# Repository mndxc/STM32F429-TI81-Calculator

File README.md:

# Neo-81: bringing new life to the classic.

## Why

The TI-81 was the first graphing calculator that was genuinely accessible for learning — affordable, approachable, and in the hands of a generation of students. It also has a look that hasn't aged: boxy, purposeful, built to last.

The problem is that the originals are now 30+ years old and the displays are failing. Rather than let them become landfill, this project replaces the internals while keeping everything that made the hardware iconic. A fresh screen, a modern MCU, and the same keypad you already know.

The end goal is a calculator you can actually use — not a shelf piece. That means completing the feature set, finishing the custom PCB, and ending up with something better than the original: same form factor, same feel, working display, and no artificial limits on what it can do.

---

## Hardware

STM32F429I-DISC1 (Cortex-M4, 180 MHz, 2.4" ILI9341 display, 8 MB SDRAM) with a salvaged TI-81 key matrix wired to the GPIO header.

**Software:** LVGL v9 · FreeRTOS · GCC ARM · CMake

---

## Status

~95% of the original TI-81 guidebook is implemented and daily-usable on the STM32F429I-DISC1 development board. Hardware validation is ongoing — see [docs/hardware_checklist.md](docs/hardware_checklist.md). A custom PCB to replace the original TI-81 internals while keeping the original shell is in design: an STM32H743 main board carrying its own 50-key keypad, plus a small display carrier board that mounts the new 2.8" panel on the original screw posts. See [hardware/](hardware/README.md).

---

## No hardware? No problem.

You can build and run the full test suite on any machine — no STM32 board required.

```bash
git clone https://github.com/mndxc/STM32F429-TI81-Calculator.git
cd STM32F429-TI81-Calculator
cmake -S App/Tests -B build-tests && cmake --build build-tests
ctest --test-dir build-tests
```

All host tests pass on plain x86/ARM Linux and macOS with any standard C compiler — see [docs/TESTING.md](docs/TESTING.md) for the current suite breakdown (16 suites, 1112 assertions). No toolchain, no board, no USB cable needed.

---

## Documentation

| I want to… | Go here |
|---|---|
| Build and flash the firmware | [docs/GETTING_STARTED.md](docs/GETTING_STARTED.md) |
| Understand the architecture | [docs/ARCHITECTURE.md](docs/ARCHITECTURE.md) |
| Read the full technical reference | [docs/TECHNICAL.md](docs/TECHNICAL.md) |
| Run the host tests | [docs/TESTING.md](docs/TESTING.md) |
| Troubleshoot common issues | [docs/TROUBLESHOOTING.md](docs/TROUBLESHOOTING.md) |
| See development process standards | [docs/MAINTENANCE_STANDARDS.md](docs/MAINTENANCE_STANDARDS.md) |
| Understand display stability and power-off behaviour | [docs/DISPLAY_STABILITY.md](docs/DISPLAY_STABILITY.md) |
| Understand power management and Stop mode | [docs/POWER_MANAGEMENT.md](docs/POWER_MANAGEMENT.md) |
| Contribute | [CONTRIBUTING.md](CONTRIBUTING.md) |
| Design the hardware (boards, enclosure) | [hardware/README.md](hardware/README.md) |

---

## What's not in this repo

Some reference material can't be published (it's copyrighted by TI or by part vendors) or is too large to be useful in git. It all lives in **one** local folder, `_reference/`, which `.gitignore` excludes as a whole. Nothing else in the tree is hand-placed and ignored; the other `.gitignore` entries are tool output (builds, caches, backups).

| `_reference/…` | What it holds | Where to get it |
|---|---|---|
| `guidebook/` | The TI-81 Guidebook (PDF and a Markdown transcription). It is the behavioural spec for every calculator feature | TI's original manual: any TI-81 guidebook scan or the printed booklet |
| `datasheets/` | Vendor datasheets for the parts in [docs/PCB_DESIGN.md](docs/PCB_DESIGN.md) and `hardware/` | Each manufacturer's product page (part numbers are in the docs) |
| `kicad-libs/` | Downloaded KiCad libraries, e.g. the CDFER JLCPCB library | KiCad's Plugin and Content Manager |
| `TI-81 Stuff/` | Teardown photos and measurements of original TI-81s | Your own calculator |

You don't need any of it to build the firmware or run the tests.

---

## Contributing

Contributions are welcome — bug fixes, feature work, or documentation improvements. See [CONTRIBUTING.md](CONTRIBUTING.md) for guidelines. All contributors are expected to follow the [Code of Conduct](CODE_OF_CONDUCT.md).

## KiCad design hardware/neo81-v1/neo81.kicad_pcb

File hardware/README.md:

# Neo-81 hardware

Everything for the physical calculator: boards, libraries and enclosure. The firmware is at the repo root, and the board design notes are in [`docs/PCB_DESIGN.md`](../docs/PCB_DESIGN.md).

| Folder | What it is | Status |
|---|---|---|
| [`h7b0-board/`](h7b0-board/) | **Next board**: STM32H743V (was H7B0), RT9471 charger, RT8059 buck, W25Q128 flash, own 50-key keypad; plus a display carrier board | Pin plan and parts list; no KiCad project yet |
| [`neo81-v1/`](neo81-v1/) | First board: keypad + power (IP5310 power bank SoC, 50 touch keys), 6-layer; connects to the STM32F429 Discovery via the J4 header. Its schematic also held an MCU draft, now in `unused-sheets/` | KiCad project plus prepared gerber/BOM/CPL exports; **never ordered** |
| [`libs/`](libs/) | Project KiCad libraries: EasyEDA/LCSC parts, IP5310, JP-USB-C, softKey key footprints | Both boards use them through `${KIPRJMOD}/../libs` |
| [`enclosure/`](enclosure/) | FreeCAD: front shell, keypad PCB outline, key footprint model; `PCBPlan.pages` | Early (Oct–Nov 2025) |
| [`KICAD_CONVENTIONS.md`](KICAD_CONVENTIONS.md) | How symbols, fields, BOM flags, rules and libraries are set up, and the pre-order checklist | Read before any KiCad work |

Datasheets, the TI-81 guidebook, teardown photos and downloaded KiCad libraries are local only, in `../_reference/` (see [What's not in this repo](../README.md#whats-not-in-this-repo)).

## Opening a board in KiCad (10.x)

1. Open `neo81-v1/neo81.kicad_pro`. Its `sym-lib-table` and `fp-lib-table` load `libs/`, so the project works from any path or clone without global library setup.
2. **The JLCPCB library is not in the repo.** Four parts (`PCM_JLCPCB-*`) come from the CDFER JLCPCB library. Install it once with *Plugin and Content Manager → Install from File…* and pick the downloaded zip (kept locally at `_reference/kicad-libs/third-party/com.github.CDFER.JLCPCB-Kicad-Library_v2025.07.18.zip`). You can also install it straight from the PCM catalogue.
3. Checks after the 2026-11-27 cleanup (`kicad-cli` 10.0.0): ERC has **1 error**: IP5310 pin 31 (LIGHT, an output) is tied to GND. Check that against the IP5310 datasheet. DRC with parity: 0 parity issues and 0 unconnected pads. The 7 starved-thermal and 6 USB-C edge-clearance findings are real copper items for the next spin. `unused-sheets/` holds the draft MCU sheet and two orphan sheets that aren't part of this board. Library messages:
   - `PCM_JLCPCB` / `PCM_JLCPCB-Diodes` not configured. Step 2 fixes this.
   - `STM32F429IITx_multi` isn't in KiCad 10's `MCU_ST_STM32F4`. The schematic uses its own stored copy.
   - Several "doesn't match copy in library" warnings. The board and schematic keep their own copies of each part; **don't run "Update from Library" in bulk** without reviewing the changes.
   - The softKey footprints refer to 3D models (`footprintv1.wrl`, `Unnamed.wrl`) that were never exported. Only the 3D view is affected. The source is `enclosure/footprintv1.FCStd`.

## Ordering and assembly

- `neo81-v1/fab-outputs/`: `jlcpcb/production_files/` holds the JLCPCB plugin export (gerbers, `BOM-neo81.csv`, `CPL-neo81.csv`). `manual-gerbers/` is a hand export, and `bom-cpl/` holds its position files. Three zipped gerber sets are export variants that were prepared but never ordered: `neo81v01.zip` (2025-11-19), `neo81MarkH.zip` (2025-11-13), and `neo81TwoBoard.zip` (2026-02-04).
- Before ordering a new board, check the parts in [`h7b0-board/PARTS_VERIFICATION.md`](h7b0-board/PARTS_VERIFICATION.md). Some library footprints must be swapped, and there are open design items.

## What git tracks

The design files are committed: `.kicad_pro`, `.kicad_sch`, `.kicad_pcb`, lib tables, project libraries, FreeCAD and fab outputs. Tool output is ignored by pattern: KiCad backups (`*-backups/`, `*-bkp-*`), caches (`*.kicad_prl`, `fp-info-cache`) and FreeCAD backups (`*.FCBak`). Datasheets and downloaded libraries are local only, under `_reference/`; see the root `.gitignore`.

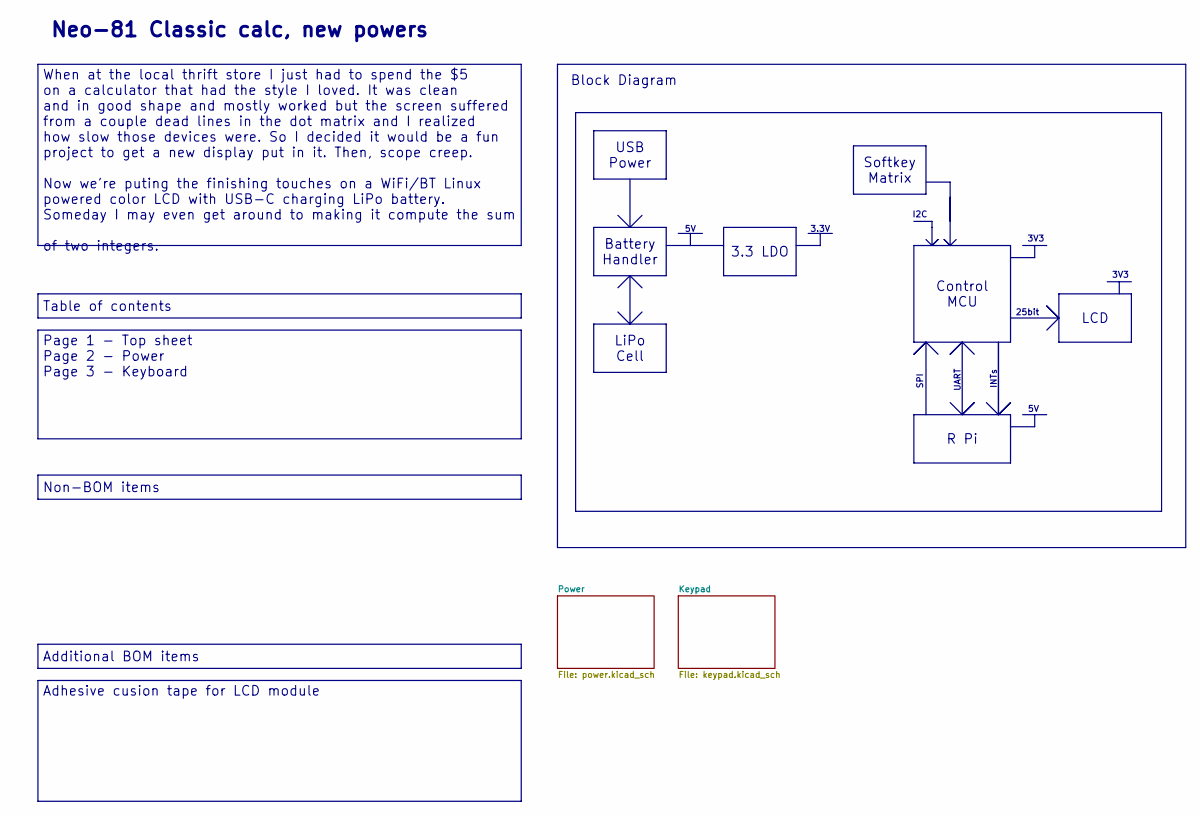
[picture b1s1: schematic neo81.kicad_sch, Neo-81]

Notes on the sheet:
INTs
Neo-81 Classic calc, new powers
Block Diagram
SPI
3V3
I2C
UART
3.3V
25bit
Control MCU
Table of contents
LCD
Non-BOM items
R Pi
Additional BOM items
When at the local thrift store I just had to spend the $5 on a calculator that had the style I loved. It was clean and in good shape and mostly worked but the screen suffered from a couple dead lines in the dot matrix and I realized how slow those devices were. So I decided it would be a fun projec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
Page 1 - Top sheet Page 2 - Power Page 3 - Keyboard
Adhesive cusion tape for LCD module
3.3 LDO
USB Power
Softkey Matrix
Battery Handler
LiPo Cell

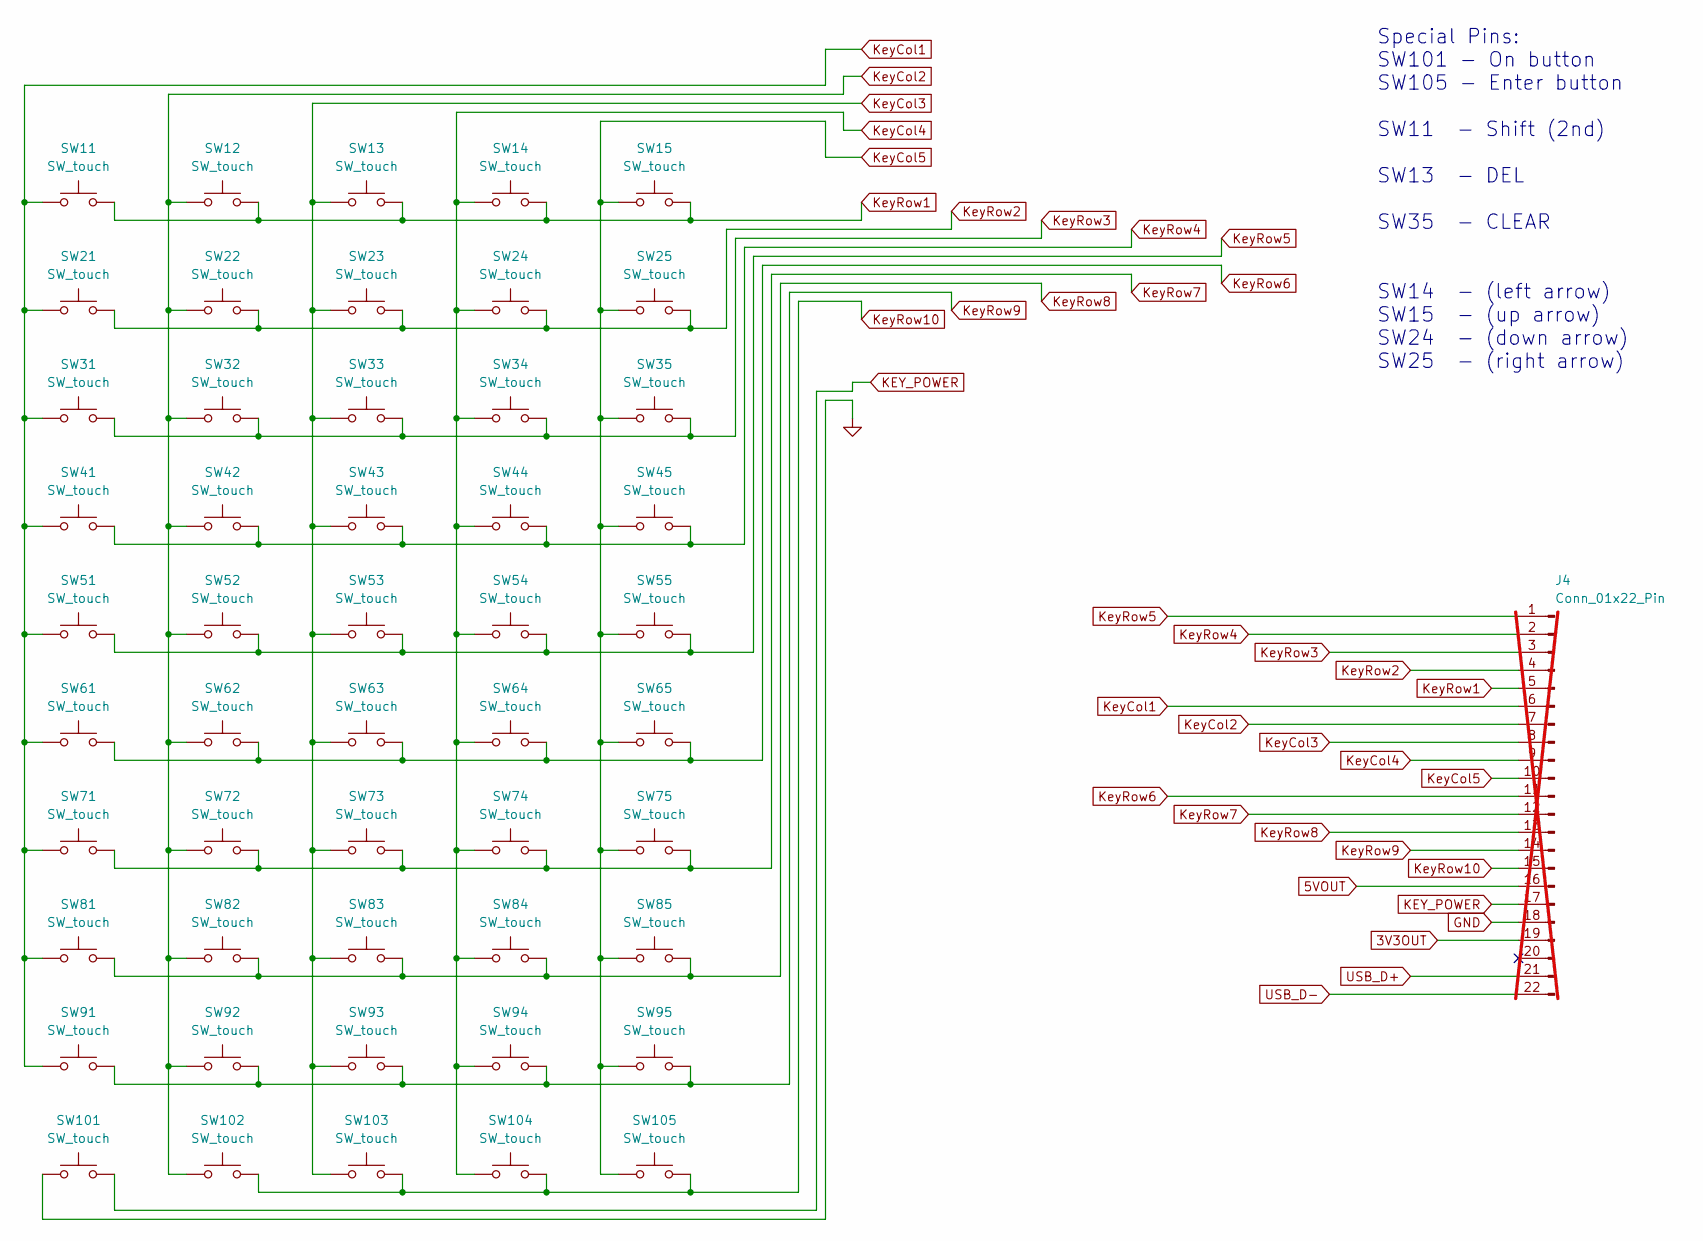
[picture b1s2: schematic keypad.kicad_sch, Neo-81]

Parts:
J4: Conn_01x22_Pin; PinHeader_1x22_P2.54mm_Vertical; not fitted
SW11, SW12, SW13, SW15, SW21, SW22, SW23, SW24, SW31, SW32, SW33, SW35, SW41, SW42, SW43, SW44, SW45, SW51, SW52, SW53, SW54, SW55, SW61, SW62, SW63, SW64, SW65, SW71, SW72, SW73, SW74, SW75, SW81, SW82, SW83, SW84, SW85, SW91, SW92, SW93, SW94, SW95, SW101, SW102, SW104, SW105: SW_touch; softkeyViaImage3
SW14, SW25, SW34, SW103: SW_touch; softkeyViaImageSmallPads

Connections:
3V3OUT: J4.19; also elsewhere on the board
5VOUT: J4.16; also elsewhere on the board
GND: J4.18, SW101.1; also elsewhere on the board
KEY_POWER: J4.17, SW101.2; also elsewhere on the board
KeyCol1: J4.6, SW11.1, SW21.1, SW31.1, SW41.1, SW51.1, SW61.1, SW71.1, SW81.1, SW91.1
KeyCol2: J4.7, SW12.1, SW22.1, SW32.1, SW42.1, SW52.1, SW62.1, SW72.1, SW82.1, SW92.1, SW102.1
KeyCol3: J4.8, SW13.1, SW23.1, SW33.1, SW43.1, SW53.1, SW63.1, SW73.1, SW83.1, SW93.1, SW103.1
KeyCol4: J4.9, SW14.1, SW24.1, SW34.1, SW44.1, SW54.1, SW64.1, SW74.1, SW84.1, SW94.1, SW104.1
KeyCol5: J4.10, SW15.1, SW25.1, SW35.1, SW45.1, SW55.1, SW65.1, SW75.1, SW85.1, SW95.1, SW105.1
KeyRow1: J4.5, SW11.2, SW12.2, SW13.2, SW14.2, SW15.2
KeyRow2: J4.4, SW21.2, SW22.2, SW23.2, SW24.2, SW25.2
KeyRow3: J4.3, SW31.2, SW32.2, SW33.2, SW34.2, SW35.2
KeyRow4: J4.2, SW41.2, SW42.2, SW43.2, SW44.2, SW45.2
KeyRow5: J4.1, SW51.2, SW52.2, SW53.2, SW54.2, SW55.2
KeyRow6: J4.11, SW61.2, SW62.2, SW63.2, SW64.2, SW65.2
KeyRow7: J4.12, SW71.2, SW72.2, SW73.2, SW74.2, SW75.2
KeyRow8: J4.13, SW81.2, SW82.2, SW83.2, SW84.2, SW85.2
KeyRow9: J4.14, SW91.2, SW92.2, SW93.2, SW94.2, SW95.2
KeyRow10: J4.15, SW102.2, SW103.2, SW104.2, SW105.2
USB_D+: J4.21; also elsewhere on the board
USB_D-: J4.22; also elsewhere on the board

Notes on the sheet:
Special Pins: SW101 - On button SW105 - Enter button SW11 - Shift (2nd) SW13 - DEL SW35 - CLEAR SW14 - (left arrow) SW15 - (up arrow) SW24 - (down arrow) SW25 - (right arrow)

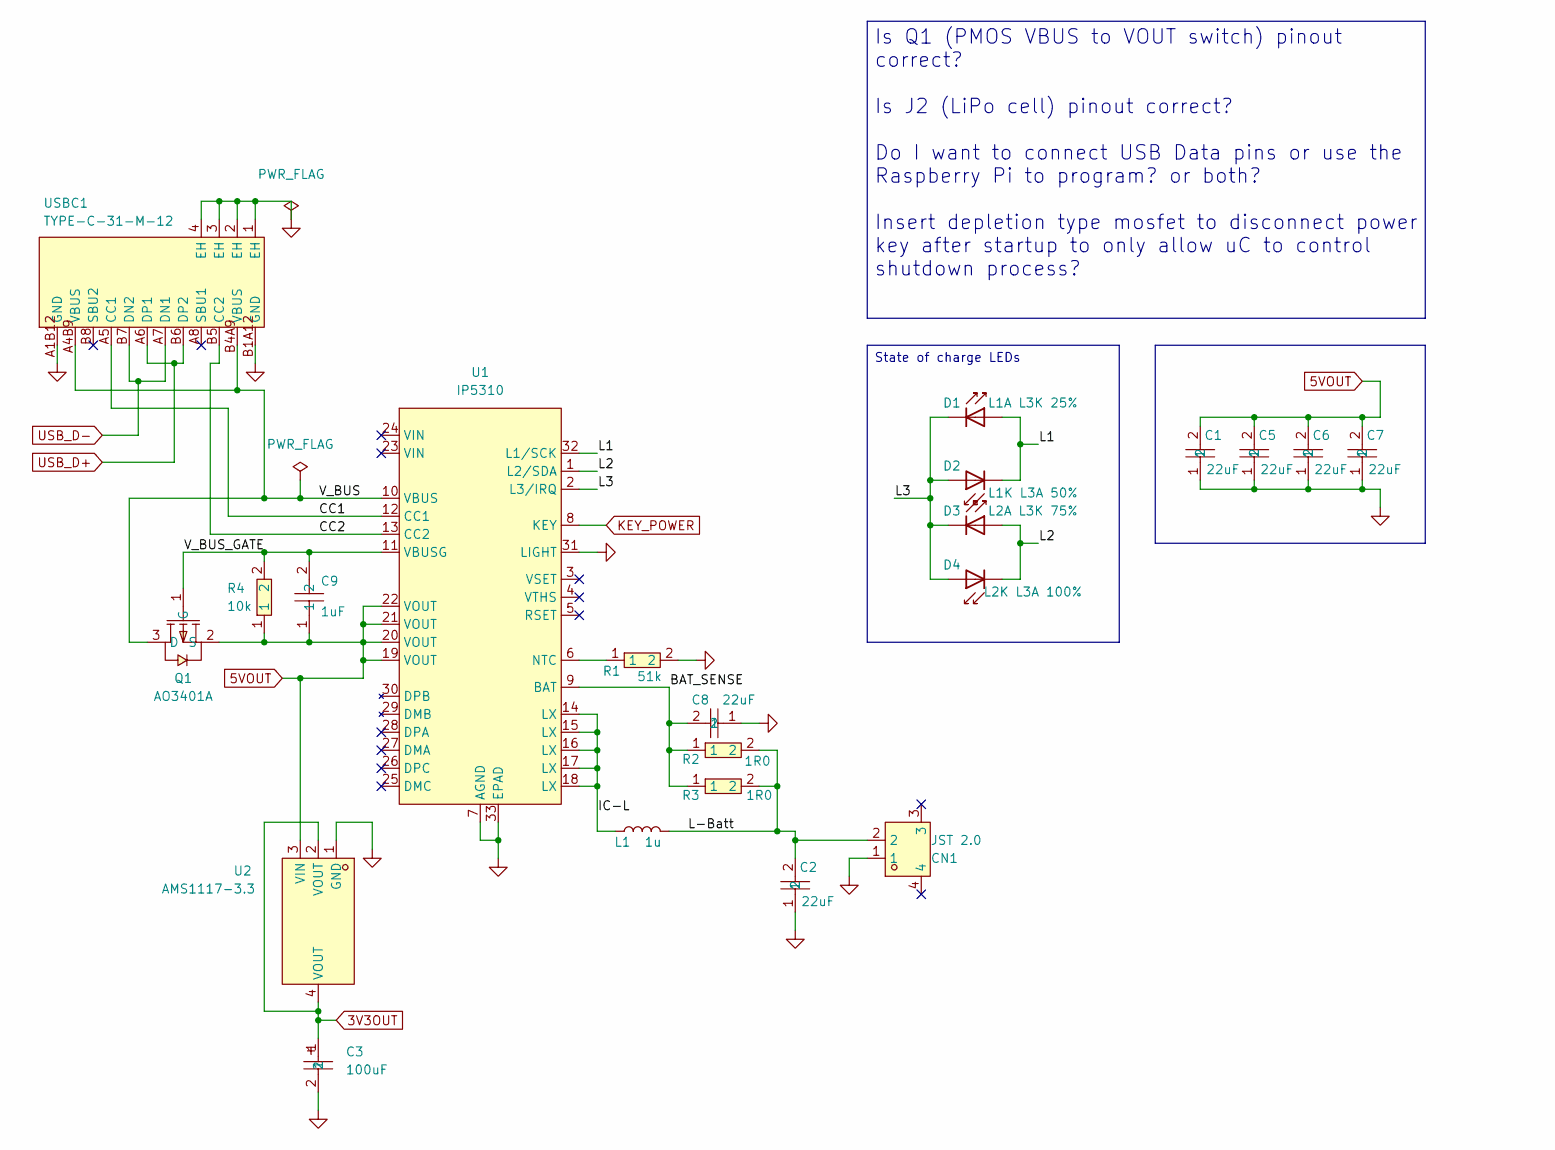
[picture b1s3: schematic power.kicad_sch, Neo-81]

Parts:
C1, C2, C5, C6, C7, C8: 22uF; C1206; MPN CL31A226KAHNNNE; LCSC C12891
C3: 100uF; CASE-B_3528; MPN TAJB107K006RNJ; LCSC C16133
C9: 1uF; C0603; MPN CL10A105KB8NNNC; LCSC C15849
CN1: JST 2.0; CONN-SMD_P2.00_S2B-PH-SM4-TB-LF-SN; MPN S2B-PH-SM4-TB(LF)(SN); LCSC C295747
D1, D2, D3, D4: Red; D_0805; MPN NCD0805R1; LCSC C84256
L1: 1u; IND-SMD_L13.8-W12.6; MPN MHCC12050-1R0M-R7; LCSC C329553
Q1: AO3401A; SOT-23_L2.9-W1.3-P1.90-LS2.4-BR; MPN AO3401A; LCSC C15127
R1: 51k; R0603; MPN 0603WAF5102T5E; LCSC C23196
R2, R3: 1R0; R0603; MPN 0603WAF100KT5E; LCSC C22936
R4: 10k; R0603; MPN 0603WAF1002T5E; LCSC C25804
U1: IP5310; QFN-32-1EP_5x5mm_P0.5mm_EP3.3x3.3mm_ThermalVias; MPN IP5310; LCSC C191176
U2: AMS1117-3.3; SOT-223-3_L6.5-W3.4-P2.30-LS7.0-BR; MPN AMS1117-3.3; LCSC C6186
USBC1: TYPE-C-31-M-12; USB-C_SMD-TYPE-C-31-M-12_1; MPN TYPE-C-31-M-12; LCSC C165948

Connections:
3V3OUT: C3.1, U2.2 (VOUT), U2.4 (VOUT); also elsewhere on the board
5VOUT: C1.2, C5.2, C6.2, C7.2, C9.1, Q1.2 (S), R4.1, U1.19 (VOUT), U1.20 (VOUT), U1.21 (VOUT), U1.22 (VOUT), U2.3 (VIN); also elsewhere on the board
/Power/BAT_SENSE: C8.2, R2.1, R3.1, U1.9 (BAT)
/Power/CC1: U1.12 (CC1), USBC1.A5 (CC1)
/Power/CC2: U1.13 (CC2), USBC1.B5 (CC2)
/Power/IC-L: L1.1, U1.14 (LX), U1.15 (LX), U1.16 (LX), U1.17 (LX), U1.18 (LX)
/Power/L1: D1.2, D2.1, U1.32 (L1/SCK)
/Power/L2: D3.2, D4.1, U1.1 (L2/SDA)
/Power/L3: D1.1, D2.2, D3.1, D4.2, U1.2 (L3/IRQ)
/Power/L-Batt: C2.2, CN1.2, L1.2, R2.2, R3.2
/Power/V_BUS: Q1.3 (D), U1.10 (VBUS), USBC1.A4B9 (VBUS), USBC1.B4A9 (VBUS)
/Power/V_BUS_GATE: C9.2, Q1.1 (G), R4.2, U1.11 (VBUSG)
GND: C1.1, C2.1, C3.2, C5.1, C6.1, C7.1, C8.1, CN1.1, R1.2, U1.7 (AGND), U1.31 (LIGHT), U1.33 (EPAD), U2.1 (GND), USBC1.1 (EH), USBC1.2 (EH), USBC1.3 (EH), USBC1.4 (EH), USBC1.A1B12 (GND), USBC1.B1A12 (GND); also elsewhere on the board
KEY_POWER: U1.8 (KEY); also elsewhere on the board
unnamed: R1.1, U1.6 (NTC)
USB_D+: USBC1.A6 (DP1), USBC1.B6 (DP2); also elsewhere on the board
USB_D-: USBC1.A7 (DN1), USBC1.B7 (DN2); also elsewhere on the board

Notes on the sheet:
Is Q1 (PMOS VBUS to VOUT switch) pinout correct? Is J2 (LiPo cell) pinout correct? Do I want to connect USB Data pins or use the Raspberry Pi to program? or both? Insert depletion type mosfet to disconnect power key after startup to only allow uC to control shutdown process?
State of charge LEDs

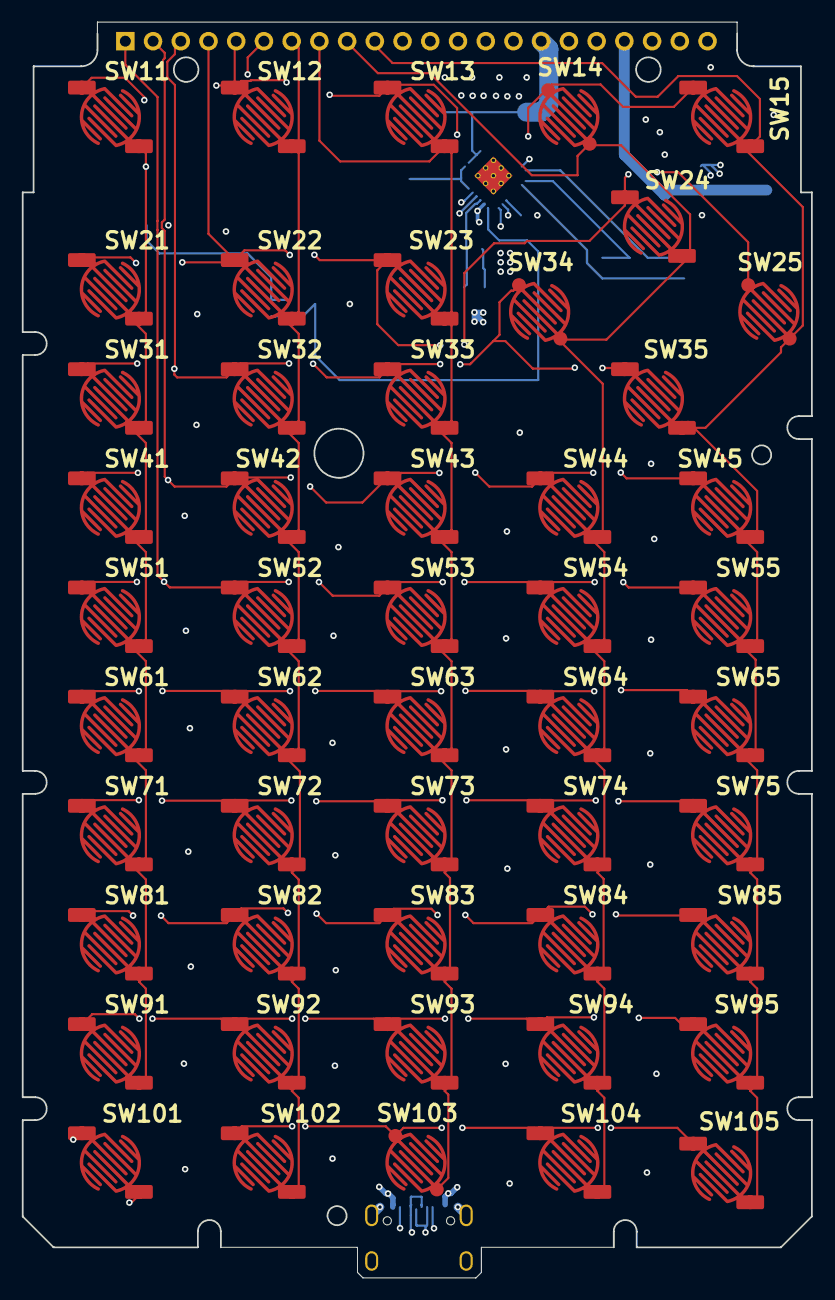
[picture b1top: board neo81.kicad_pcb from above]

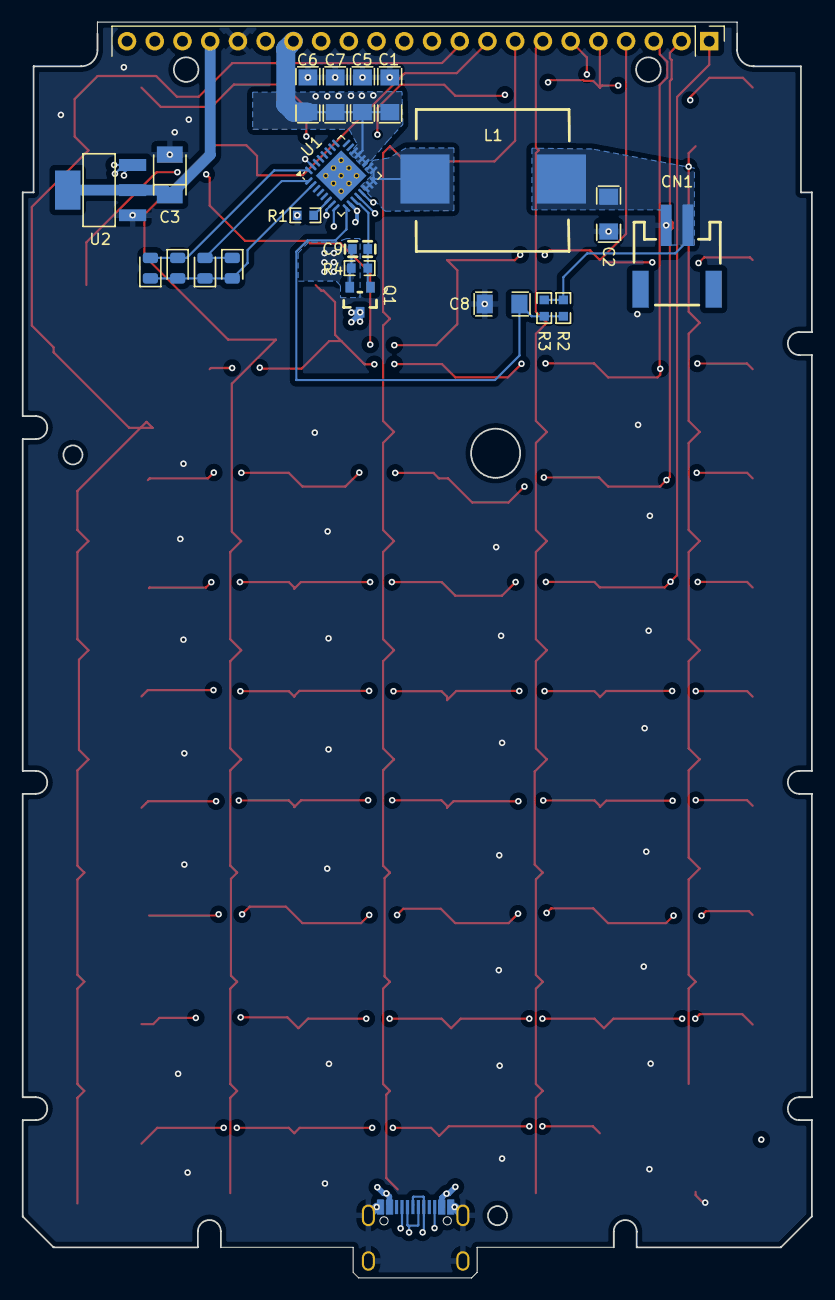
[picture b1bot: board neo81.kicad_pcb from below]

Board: 6 copper layers, 72.3 x 115.1 mm, 73 parts (23 on the bottom side), 32 nets.

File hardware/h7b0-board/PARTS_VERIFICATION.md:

# H7B0 board: parts verification

**Checked 2026-11-27.** Each part's symbol, pinout, and footprint in the datasheets.md library (workspace "Personal") were compared with the manufacturer's original PDF. The service's own extracted text was not used. The STM32 was checked by script: all 100 LQFP100 pins against ST's Table 7. The tool notes and raw coverage results are in `~/Projects/Reference/KiCad-Tools/datasheets-md/`.

## Library parts

| Part | Pinout vs datasheet | Footprint | Verdict |
|---|---|---|---|
| STM32H7B0VBT6 | ✅ 100/100 (KiCad's own `STM32H7B0VBTx` symbol) | ✅ LQFP-100 14×14 P0.5 | Use |
| W25Q128JVSIQ | ✅ 8/8, active-low /CS /WP /HOLD marked | ✅ SOIC-8 5.3×5.3 (208-mil) | Use |
| RT8059GJ5 | ✅ EN, GND, LX, VIN, FB | ✅ TSOT-23-5 | Use (generated box symbol) |
| RT4812GJ8F | ✅ 8/8 | ✅ TSOT-23-8 (Richtek land pattern: P 0.65, pad 1.0×0.45) | Use (generated box symbol) |
| RT9471GQW | ✅ 25/25 (plain RT9471) | ⚠️ generated from the outline drawing; the land pattern was not read | Use the symbol. **Swap the footprint for KiCad `QFN-24-1EP_4x4mm_P0.5mm_EP2.6x2.6mm`**, which matches Richtek Option 2 (Sx = Sy = 2.60) |
| TPD4E05U06DQAR | ✅ 10/10 | ✅ USON-10 2.5×1.0 | Use. TI makes this part only in USON-10 (DQA). NC pins 6, 7, 9 and 10 are for optional straight-through routing |
| AO3401A | ✅ G/S/D = 1/2/3 | ✅ SOT-23 | Use. S and D are typed power_in, which causes cosmetic ERC noise only |
| BAT54WS-7-F | ✅ 1 = K, 2 = A | ✅ SOD-323 | Use |
| JST S2B-PH-SM4-TB | pins OK | ❌ none | Use KiCad `Connector_JST:JST_PH_S2B-PH-SM4-TB_1x02-1MP_P2.00mm_Horizontal` |
| TYPE-C-31-M-12 | numbered 1–16, not A1–B12, no shield | ❌ none | Don't use. Use `libs/JP-USB-C.kicad_sym` with the EasyEDA footprint |

Not in the library: the ER-TFT028A2-4 display and IP5310 (neither is on DigiKey), and AMS1117-3.3, for which only UTD's SOT-89 version is listed. Passives use KiCad's built-in symbols.

Nothing is marked "reviewed" in datasheets.md yet.

## Charger USB detection: RT9471 vs RT9471D (evaluated 2026-11-27)

**Where the question came from.** `docs/PCB_DESIGN.md` lists the **RT9471** in the BOM. It also says the ESD part goes "before the RT9471 D+/D− pins". The plain RT9471 has no D+/D− pins: its pins 2 and 3 are PSEL and PG. Only the **RT9471D** has D+/D−, which it uses for BC1.2 charger-type detection. It drops PSEL and PG, and swaps VBUS and VAC between pins 1 and 24. The two lines contradict each other, and no other doc records a requirement for BC1.2 detection. So the D+/D− line looks like a doc mistake, not a design decision.

**What each variant gets you:**

| | RT9471 (BOM today) | RT9471D |
|---|---|---|
| How it picks the input current limit | The PSEL pin (high = 0.5 A, low = 2.4 A), then firmware sets AICR over I²C | Automatic BC1.2 detection on D+/D− (SDP, CDP or DCP) |
| What that detection helps | — | Only **legacy USB-A chargers on an A-to-C cable**. USB-C chargers advertise current on **CC**, which neither chip reads |
| USB data to the MCU | D+/D− go straight to the STM32 (PA11/PA12, internal FS PHY) | D+/D− would be shared between the charger and the STM32, so the STM32's D+ pull-up and the BC1.2 detection phase have to be kept from clashing |
| Extra pins | PG power-good output | — |

The STM32H7B0's own OTG_HS supports **BC1.2** (datasheet §3.47), so the MCU can detect legacy chargers itself if that's ever wanted.

**Recommendation: keep the plain RT9471** and correct the doc:
1. Route USB D+/D− to the **STM32 (PA11/PA12)**, not the charger. That keeps USB data available: the ROM bootloader's USB DFU gives firmware updates without an ST-Link (confirm the H7B0 entry in ST AN2606), and it leaves room for program or variable transfer later.
2. **Add 5.1 kΩ pull-downs (Rd) on CC1 and CC2. They're missing from the design today.** Without them, USB-C to USB-C chargers won't turn on VBUS at all.
3. Tie **PSEL high** for a safe 0.5 A default. At boot, firmware reads the CC voltage with the ADC (Default, 1.5 A or 3 A advertisement) and only then raises AICR to 1.5 A. Setting 1.5 A unconditionally, as `PCB_DESIGN.md` says now, overdraws a 500 mA computer port. The RT9471's VBUS voltage regulation (VINDPM) would limit the damage, but it's still out of spec.
4. The 4-channel TPD4E05U06 can cover D+, D−, CC1 and CC2.

The RT9471D would only make sense if the calculator never used USB data and you wanted fast charging from old USB-A bricks with no firmware involved. Neither seems to be a goal.

**Still to confirm before layout:** JLCPCB/LCSC stock for **RT9471GQW** specifically (`PCB_DESIGN.md` says "all verified on JLCPCB" but doesn't name the variant); the CC-sensing ADC pins and divider; and AN2606 USB DFU support on PA11/PA12 for the H7B0.
